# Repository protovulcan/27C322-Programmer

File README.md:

# ST27C322 EPROM Programmer

This schematic is for an EPROM programmer that I put together to allow me to build a switchable Amiga Kickstart.  The plan is to put DiagROM and Kickstarts v1.3, v2.4, and v3.1.1 on a single EPROM. It uses a boost converter to generate the programming voltage _VPP_ so it can be run from USB only. It uses [MCP23017](./docs/MCP23017-datasheet.pdf) IO extenders to generate enough Address and Data lines. The Data lines are driven by the io extender at ```0x20``` while the high data lines are driven by the io extender at ```0x24```.

The current state of this board is alpha. The drill holes for the socket are too small and there are things that need to be properly tested.

The intention with the firmware is to make it handle intel hex via terminal with an ```PASSED``` or:

>
> ERR @ b###########: 0x#### != 0x####
>

# Pinout 

| Arduino | Connected |
|-|-|
| D5 | Address 0 |
| D6 | Address 1 |
| D7 | Address 2 |
| D8 | Address 3 |
| D9 | Address 4 |
| D10 | Programmer Enable - turns on boost converter |
| A0 | INTB on Address io extender |
| A1 | INTA on Address io extender |
| A2 | INTB on Data io extender |
| A3 | INTA on Data io extender |
| A4 | SDA of I2C bus |
| A5 | SDC of I2C bus |
| A6 | RESET of io extender |
| A7 | ENABLE for EEPROM |

# Schematic 

The following schematic was made with KiCAD 5.1.5.  It is currently inadequtely tested.

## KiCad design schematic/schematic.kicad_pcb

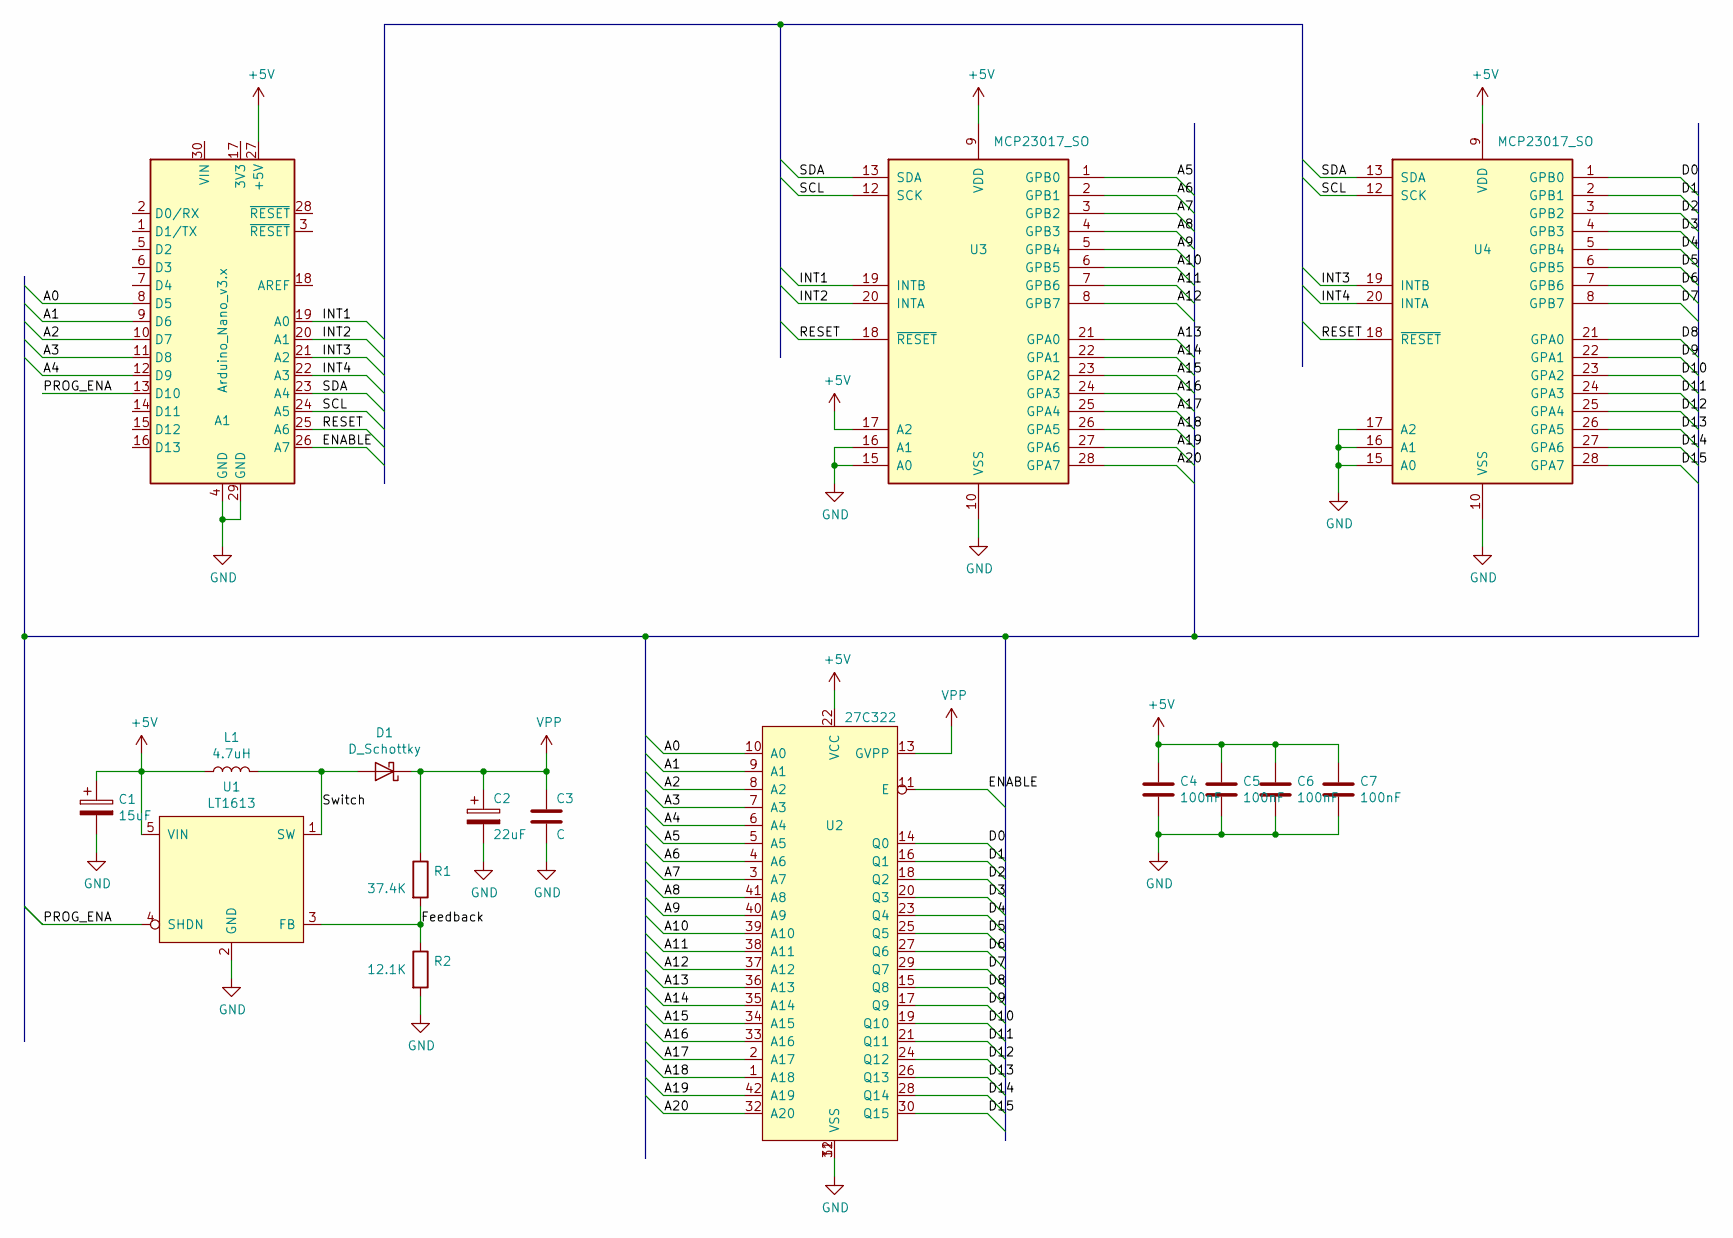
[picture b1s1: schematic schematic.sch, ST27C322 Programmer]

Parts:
A1: Arduino_Nano_v3.x; Arduino_Nano
C1: 15uF; C_Elec_8x6.2
C2: 22uF; C_Elec_8x6.2
C3: C; C_1210_3225Metric
C4, C5, C6, C7: 100nF; R_1206_3216Metric
D1: D_Schottky; R_1206_3216Metric
L1: 4.7uH; L_10.4x10.4_H4.8
R1: 37.4K; R_1206_3216Metric
R2: 12.1K; R_1206_3216Metric
U1: LT1613; SOT-23-5_HandSoldering
U2: 27C322; DIP-42_W15.24mm_Socket_LongPads
U3, U4: MCP23017_SO; SOIC-28W_7.5x17.9mm_P1.27mm

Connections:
+5V: A1.27 (+5V), C1.1, C4.1, C5.1, C6.1, C7.1, L1.1, U1.5 (VIN), U2.22 (VCC), U3.9 (VDD), U3.17 (A2), U4.9 (VDD)
/A0: A1.8 (D5), U2.10 (A0)
/A1: A1.9 (D6), U2.9 (A1)
/A2: A1.10 (D7), U2.8 (A2)
/A3: A1.11 (D8), U2.7 (A3)
/A4: A1.12 (D9), U2.6 (A4)
/A5: U2.5 (A5), U3.1 (GPB0)
/A6: U2.4 (A6), U3.2 (GPB1)
/A7: U2.3 (A7), U3.3 (GPB2)
/A8: U2.41 (A8), U3.4 (GPB3)
/A9: U2.40 (A9), U3.5 (GPB4)
/A10: U2.39 (A10), U3.6 (GPB5)
/A11: U2.38 (A11), U3.7 (GPB6)
/A12: U2.37 (A12), U3.8 (GPB7)
/A13: U2.36 (A13), U3.21 (GPA0)
/A14: U2.35 (A14), U3.22 (GPA1)
/A15: U2.34 (A15), U3.23 (GPA2)
/A16: U2.33 (A16), U3.24 (GPA3)
/A17: U2.2 (A17), U3.25 (GPA4)
/A18: U2.1 (A18), U3.26 (GPA5)
/A19: U2.42 (A19), U3.27 (GPA6)
/A20: U2.32 (A20), U3.28 (GPA7)
/D0: U2.14 (Q0), U4.1 (GPB0)
/D1: U2.16 (Q1), U4.2 (GPB1)
/D2: U2.18 (Q2), U4.3 (GPB2)
/D3: U2.20 (Q3), U4.4 (GPB3)
/D4: U2.23 (Q4), U4.5 (GPB4)
/D5: U2.25 (Q5), U4.6 (GPB5)
/D6: U2.27 (Q6), U4.7 (GPB6)
/D7: U2.29 (Q7), U4.8 (GPB7)
/D8: U2.15 (Q8), U4.21 (GPA0)
/D9: U2.17 (Q9), U4.22 (GPA1)
/D10: U2.19 (Q10), U4.23 (GPA2)
/D11: U2.21 (Q11), U4.24 (GPA3)
/D12: U2.24 (Q12), U4.25 (GPA4)
/D13: U2.26 (Q13), U4.26 (GPA5)
/D14: U2.28 (Q14), U4.27 (GPA6)
/D15: U2.30 (Q15), U4.28 (GPA7)
/ENABLE: A1.26 (A7), U2.11 (E)
/Feedback: R1.2, R2.1, U1.3 (FB)
/INT1: A1.19 (A0), U3.19 (INTB)
/INT2: A1.20 (A1), U3.20 (INTA)
/INT3: A1.21 (A2), U4.19 (INTB)
/INT4: A1.22 (A3), U4.20 (INTA)
/PROG_ENA: A1.13 (D10), U1.4 (SHDN)
/RESET: A1.25 (A6), U3.18 (~RESET~), U4.18 (~RESET~)
/SCL: A1.24 (A5), U3.12 (SCK), U4.12 (SCK)
/SDA: A1.23 (A4), U3.13 (SDA), U4.13 (SDA)
/Switch: D1.2 (A), L1.2, U1.1 (SW)
GND: A1.4 (GND), A1.29 (GND), C1.2, C2.2, C3.2, C4.2, C5.2, C6.2, C7.2, R2.2, U1.2 (GND), U2.12 (VSS), U2.31 (VSS), U3.10 (VSS), U3.15 (A0), U3.16 (A1), U4.10 (VSS), U4.15 (A0), U4.16 (A1), U4.17 (A2)
VPP: C2.1, C3.1, D1.1 (K), R1.1, U2.13 (GVPP)

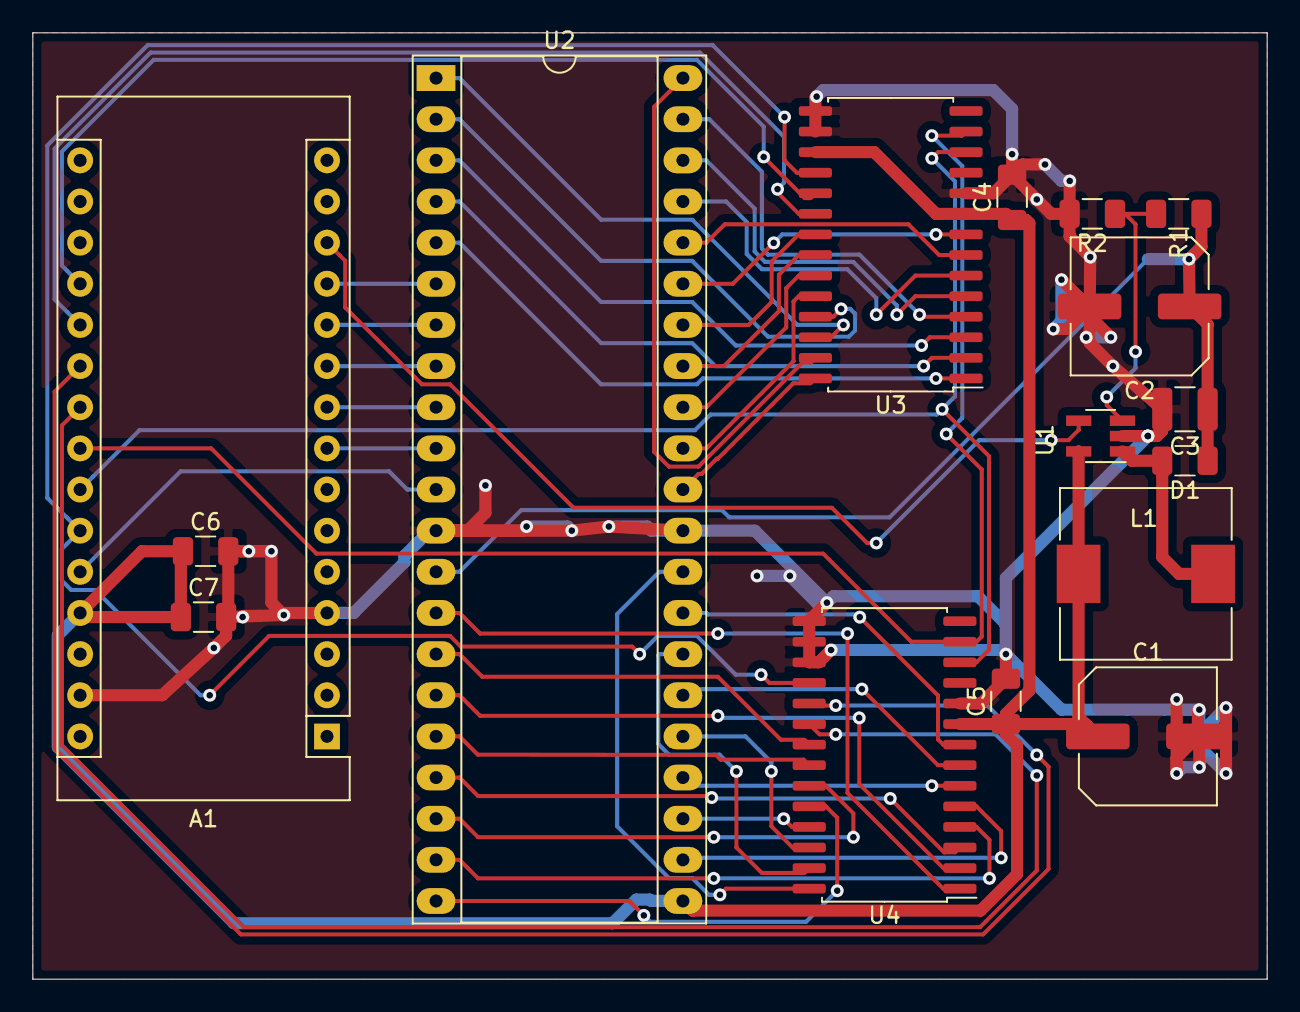
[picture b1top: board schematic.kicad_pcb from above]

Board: 2 copper layers, 76.2 x 58.4 mm, 16 parts (0 on the bottom side), 51 nets.

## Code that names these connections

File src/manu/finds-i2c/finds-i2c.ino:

#include <Wire.h>


#define ADDR0 5 // D5
#define ADDR1 6 // D6
#define ADDR2 7 // D7
#define ADDR3 8 // D8
#define ADDR4 9 // D9
#define ENABLE 10 // D10
#define INT1 14 // A0
#define INT2 15 // A1
#define INT3 16 // A2
#define INT4 17 // A3
#define RESET  12 // A6 - fuck bodge wire time
#define ENABLE 11 // A7 - fuck bodge wire time


void setup()
{
    pinMode(RESET, OUTPUT);
    pinMode(ENABLE, OUTPUT);
    pinMode(ADDR0, OUTPUT);
    pinMode(ADDR1, OUTPUT);
    pinMode(ADDR2, OUTPUT);
    pinMode(ADDR3, OUTPUT);
    pinMode(ADDR4, OUTPUT);
    pinMode(INT1, INPUT);
    pinMode(INT2, INPUT);
    pinMode(INT3, INPUT);
    pinMode(INT4, INPUT);
    Wire.begin();
    delay(100);
    Serial.begin(115200);
    Serial.println('I2C Scan');
    reset();
    delay(100);
}

void reset() 
{
    digitalWrite(RESET,0);
    delay(50);
    digitalWrite(RESET,1);
}

void phex(byte address)
{
    if (address < 16) Serial.print("0");
    Serial.print(address, HEX);
}

void loop()
{
    byte error, address;

    for (address = 1; address < 127; address++)
    {
        Wire.beginTransmission(address);
        error = Wire.endTransmission();

        phex(address);

        Serial.print(" ");
        Serial.println(error, HEX);
    }

    delay(5000); // wait 5 seconds for next scan
}

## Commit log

2020-03-06 Progress with the building and testing
2020-03-06 Added pic
2020-03-09 Test code to work out if I2C is doing what it should
2020-03-09 Cleanup and add in the eeprom lib
